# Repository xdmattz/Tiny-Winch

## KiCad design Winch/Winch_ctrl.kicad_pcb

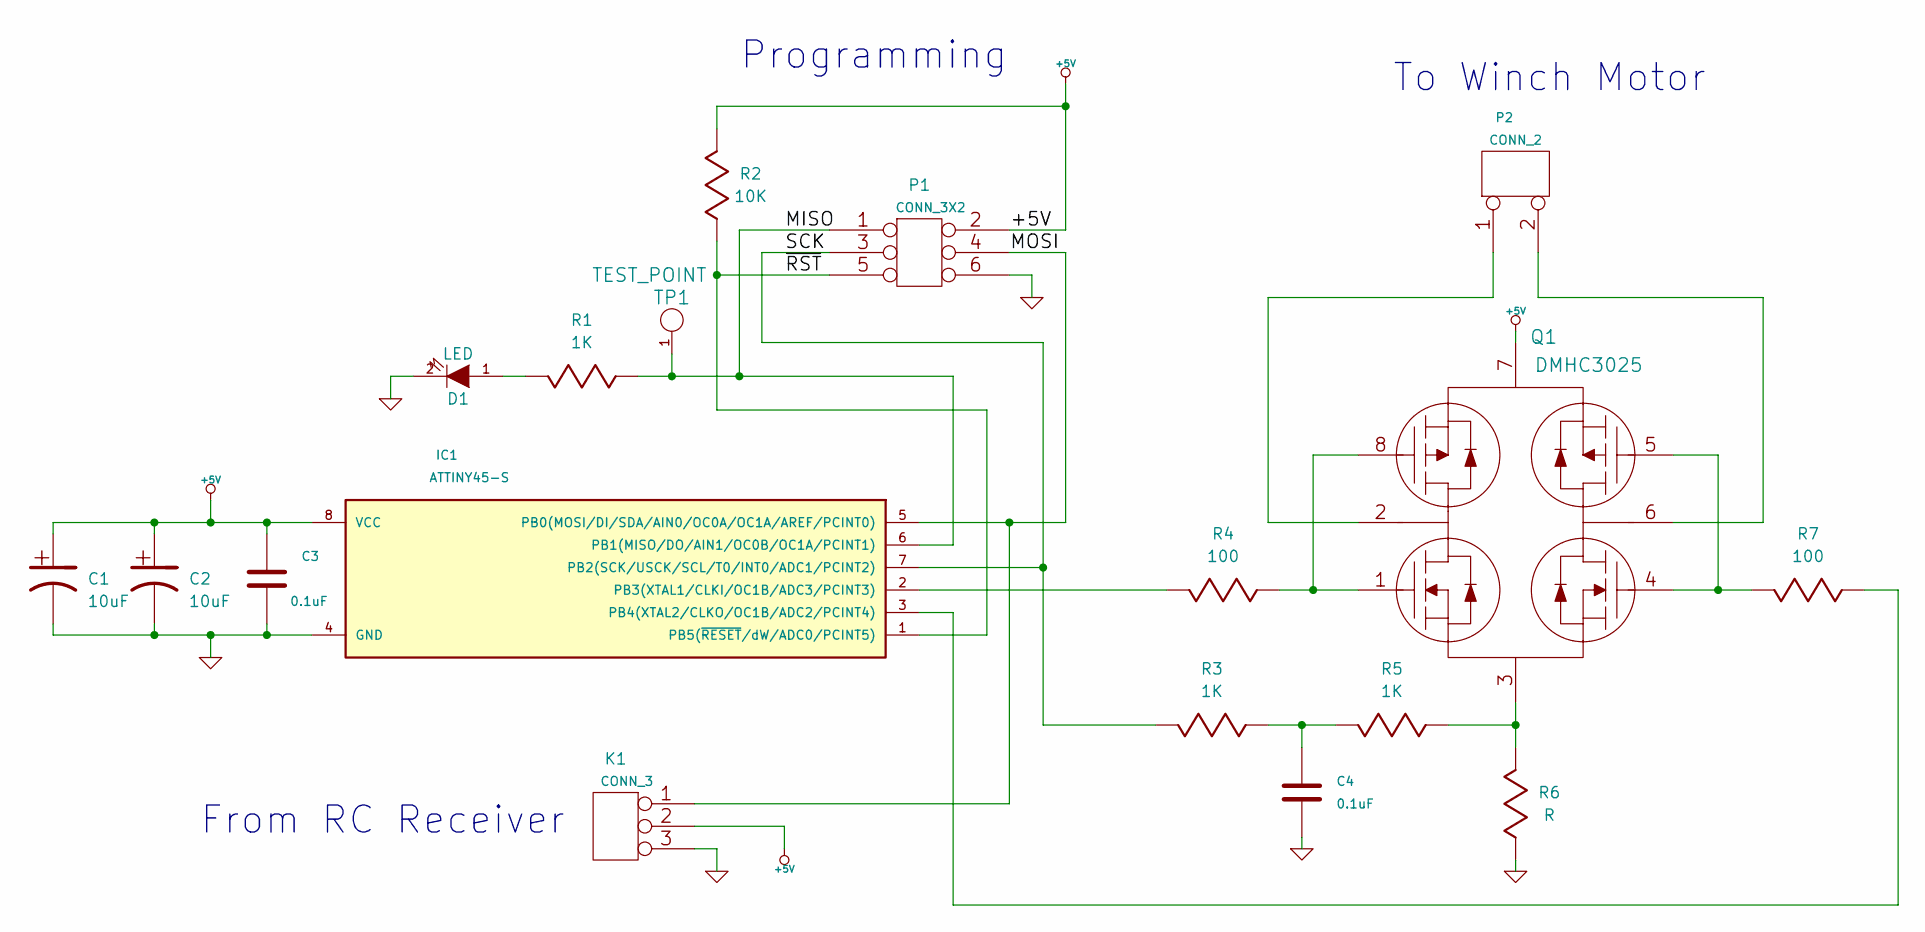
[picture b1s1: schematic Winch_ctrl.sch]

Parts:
C1, C2: 10uF; c_tant_B
C3, C4: 0.1uF; SM0603_Resistor
D1: LED; LED-0805
IC1: ATTINY45-S; tssop-8
K1: CONN_3; Pin_Header_Straight_1x03
P1: CONN_3X2; Header_3x2x050_th
P2: CONN_2; Pin_Header_Straight_1x02
Q1: DMHC3025; so-8
R1, R3, R5: 1K; SM0603_Resistor
R2: 10K; SM0603_Resistor
R4, R7: 100; SM0603_Resistor
R6: R; SM1210
TP1: TEST_POINT; TP20

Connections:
+5V: C1.1, C2.1, C3.1, IC1.8 (VCC), K1.2 (PM), P1.2, Q1.7 (P1SP2S), R2.2
/MISO: IC1.6 (PB1(MISO/DO/AIN1/OC0B/OC1A/PCINT1)), P1.1, R1.1, TP1.1
/MOSI: IC1.5 (PB0(MOSI/DI/SDA/AIN0/OC0A/OC1A/AREF/PCI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), K1.1, P1.4
/SCK: IC1.7 (PB2(SCK/USCK/SCL/T0/INT0/ADC1/PCINT2)), P1.3, R3.2
/~RST: IC1.1 (PB5(~RESET~/dW/ADC0/PCINT5)), P1.5, R2.1
GND: C1.2, C2.2, C3.2, C4.2, D1.2 (K), IC1.4 (GND), K1.3, P1.6, R6.1
unnamed: C4.1, R3.1, R5.2
unnamed: D1.1 (A), R1.2
unnamed: IC1.2 (PB3(XTAL1/CLKI/OC1B/ADC3/PCINT3)), R4.2
unnamed: IC1.3 (PB4(XTAL2/CLKO/OC1B/ADC2/PCINT4)), R7.1
unnamed: P2.1, Q1.2 (N1DP1D)
unnamed: P2.2 (PM), Q1.6 (N2DP2D)
unnamed: Q1.1 (N1G), Q1.8 (P1G), R4.1
unnamed: Q1.3 (N1SN2S), R5.1, R6.2
unnamed: Q1.4 (N2G), Q1.5 (P2G), R7.2

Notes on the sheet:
To Winch Motor
From RC Receiver
Programming

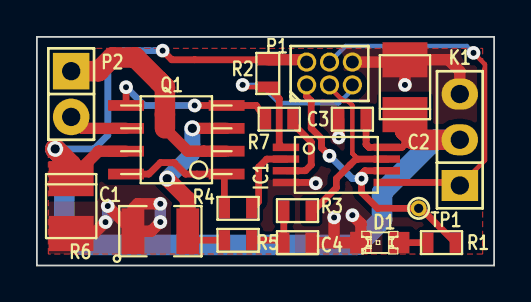
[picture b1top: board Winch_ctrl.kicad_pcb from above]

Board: 2 copper layers, 25.4 x 12.7 mm, 18 parts (0 on the bottom side), 15 nets.
